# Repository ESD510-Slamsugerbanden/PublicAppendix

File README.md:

# PublicAppendix
Public Appendix for the 5th semester project. Consisting of test data.

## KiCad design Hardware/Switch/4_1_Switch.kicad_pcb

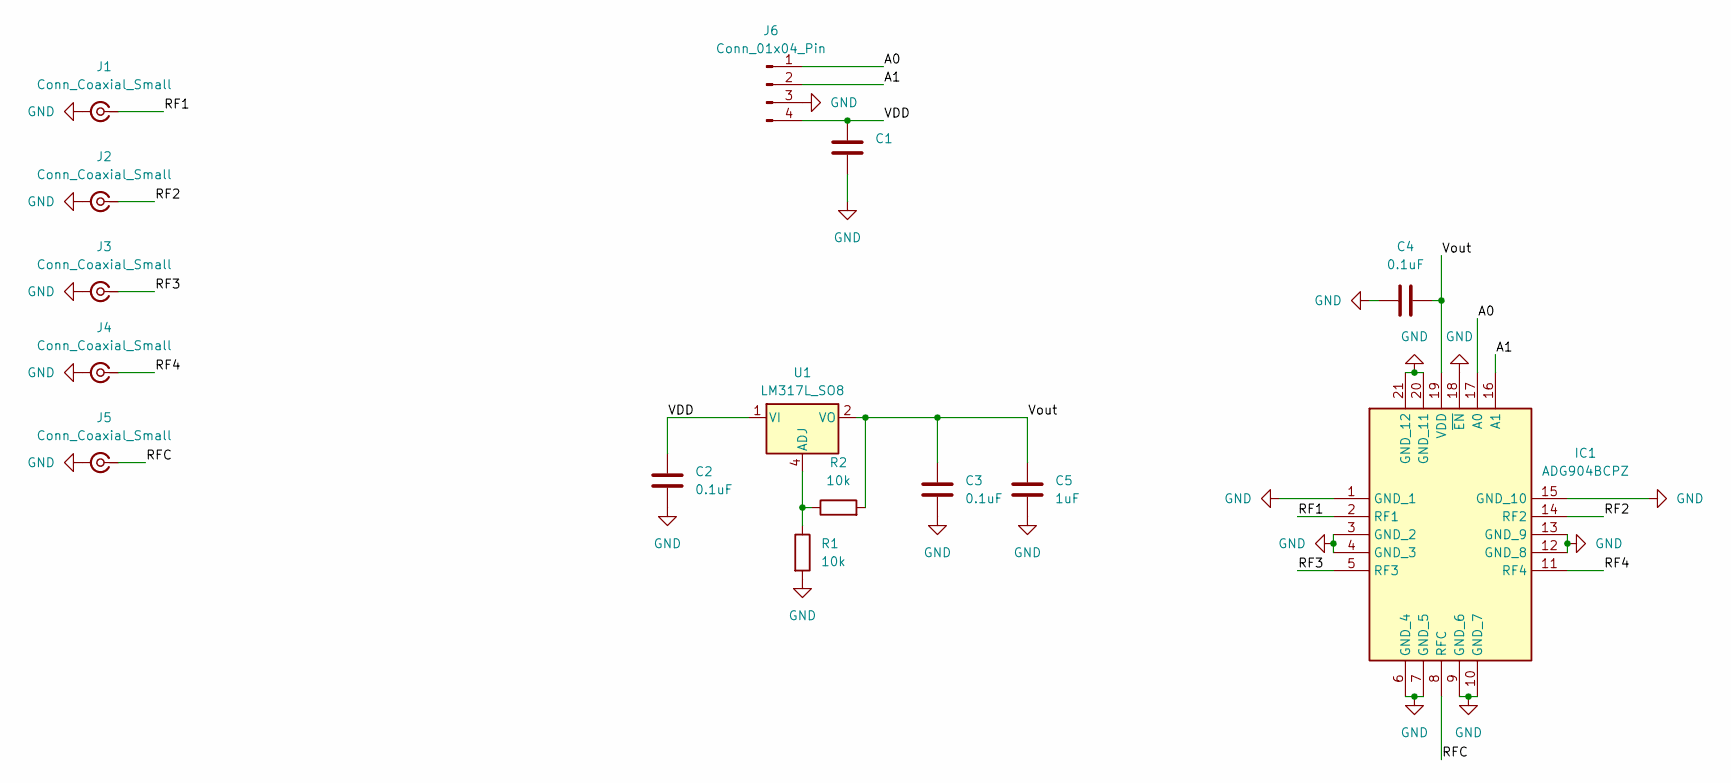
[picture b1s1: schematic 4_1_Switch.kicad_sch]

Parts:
C1: C_0805_2012Metric_Pad1.18x1.45mm_HandSolder
C2, C3, C4: 0.1uF; C_0805_2012Metric_Pad1.18x1.45mm_HandSolder
C5: 1uF; C_0805_2012Metric_Pad1.18x1.45mm_HandSolder
IC1: ADG904BCPZ; Manufacturer_Part_Number ADG904BCPZ; Mouser Part Number 584-ADG904BCPZ
J1, J2, J3, J4, J5: Conn_Coaxial_Small; SMA_Samtec_SMA-J-P-H-ST-EM1_EdgeMount
J6: Conn_01x04_Pin; JST_XH_B4B-XH-AM_1x04_P2.50mm_Vertical
R1, R2: 10k; R_0805_2012Metric_Pad1.20x1.40mm_HandSolder
U1: LM317L_SO8; SOIC-8_3.9x4.9mm_P1.27mm

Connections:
/A0: IC1.17 (A0), J6.1
/A1: IC1.16 (A1), J6.2
/RF1: IC1.2 (RF1), J1.1 (In)
/RF2: IC1.14 (RF2), J2.1 (In)
/RF3: IC1.5 (RF3), J3.1 (In)
/RF4: IC1.11 (RF4), J4.1 (In)
/RFC: IC1.8 (RFC), J5.1 (In)
/VDD: C1.1, C2.1, J6.4, U1.1 (VI)
/Vout: C3.1, C4.2, C5.1, IC1.19 (VDD), R2.2, U1.2 (VO), U1.3 (VO), U1.6 (VO), U1.7 (VO)
GND: C1.2, C2.2, C3.2, C4.1, C5.2, IC1.1 (GND_1), IC1.3 (GND_2), IC1.4 (GND_3), IC1.6 (GND_4), IC1.7 (GND_5), IC1.9 (GND_6), IC1.10 (GND_7), IC1.12 (GND_8), IC1.13 (GND_9), IC1.15 (GND_10), IC1.18 (~EN), IC1.20 (GND_11), IC1.21 (GND_12), J1.2 (Ext), J2.2 (Ext), J3.2 (Ext), J4.2 (Ext), J5.2 (Ext), J6.3, R1.2
unnamed: R1.1, R2.1, U1.4 (ADJ)

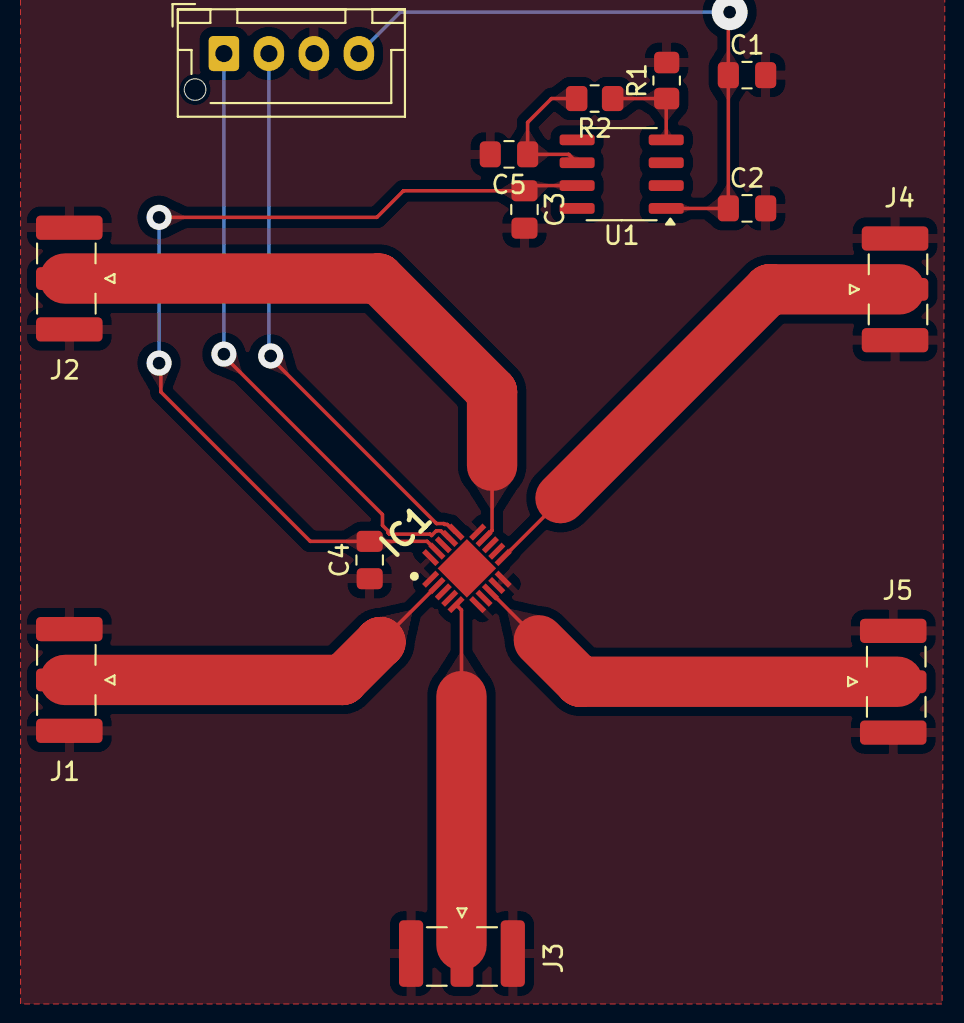
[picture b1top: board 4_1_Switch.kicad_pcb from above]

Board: 2 copper layers, 15 parts (0 on the bottom side), 11 nets.

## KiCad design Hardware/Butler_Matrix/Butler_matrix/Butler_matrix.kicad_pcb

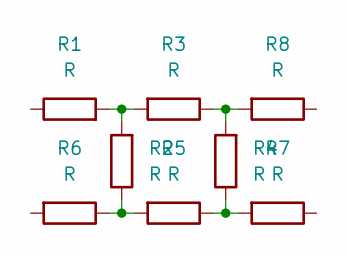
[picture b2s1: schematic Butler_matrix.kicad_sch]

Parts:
R1, R2, R4, R6, R7, R8: R; zo_245GHz
R3, R5: R; Hybrid_part

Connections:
unnamed: R1.2, R2.2, R3.2
unnamed: R2.1, R5.2, R6.1
unnamed: R3.1, R4.2, R8.2
unnamed: R4.1, R5.1, R7.2

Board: 2 copper layers, 8 parts (0 on the bottom side), 4 nets, no tracks yet.

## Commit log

2025-12-05 added rotation data
2025-12-17 Added Platform CTRL files
    Files, including measurements, matlab script and simulink simulation for PID with saturation anti-windup mm..
2025-12-18 Reciever for gnuradio
2025-12-18 Added SNR test
2025-12-18 Added initial search data and python scripts
2025-12-18 More files and functional code
2025-12-19 Update readme.md with file descriptions
    Added descriptions for various Python files in the TARM codebase.
2025-12-19 Update readme.md with initial search details
    Added details about the initial search test results and related files.
2025-12-19 Fix formatting and add colons in readme
    Correct formatting and add missing colons in the readme.
2025-12-19 Create README for Gnuradio software components
    Added a README file explaining the Gnuradio software components and their functionalities.
2025-12-19 readme
2025-12-19 Stationary accuracy tests
2025-12-19 Added Hardware files, mainly Kicad
2025-12-19 Added inventor files for the entire platform mm.
